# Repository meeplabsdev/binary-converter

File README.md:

# Binary Converter

Need to quickly convert a decimal or hex number (0-F) into binary? Now you can, with the press of two buttons.

## Schematic

## PCB

## How to build
Just order the PCB & components, open up the KiCAD file and build it accordingly.

## BOM
- 2 	Battery holder
- 8	  NPN Transistor
- 8 	47k Resistor
- 4  	4.7k Resistor
- 4 	220 Resistor
- 1 	Potentiometer
- 8 	Push Button
- 4   LED

Made by [`@19benfielde (<@U08JNMG6L00>)`](https://hackclub.slack.com/team/U08JNMG6L00) on slack :D

Made as a part of http://solder.hackclub.com/!

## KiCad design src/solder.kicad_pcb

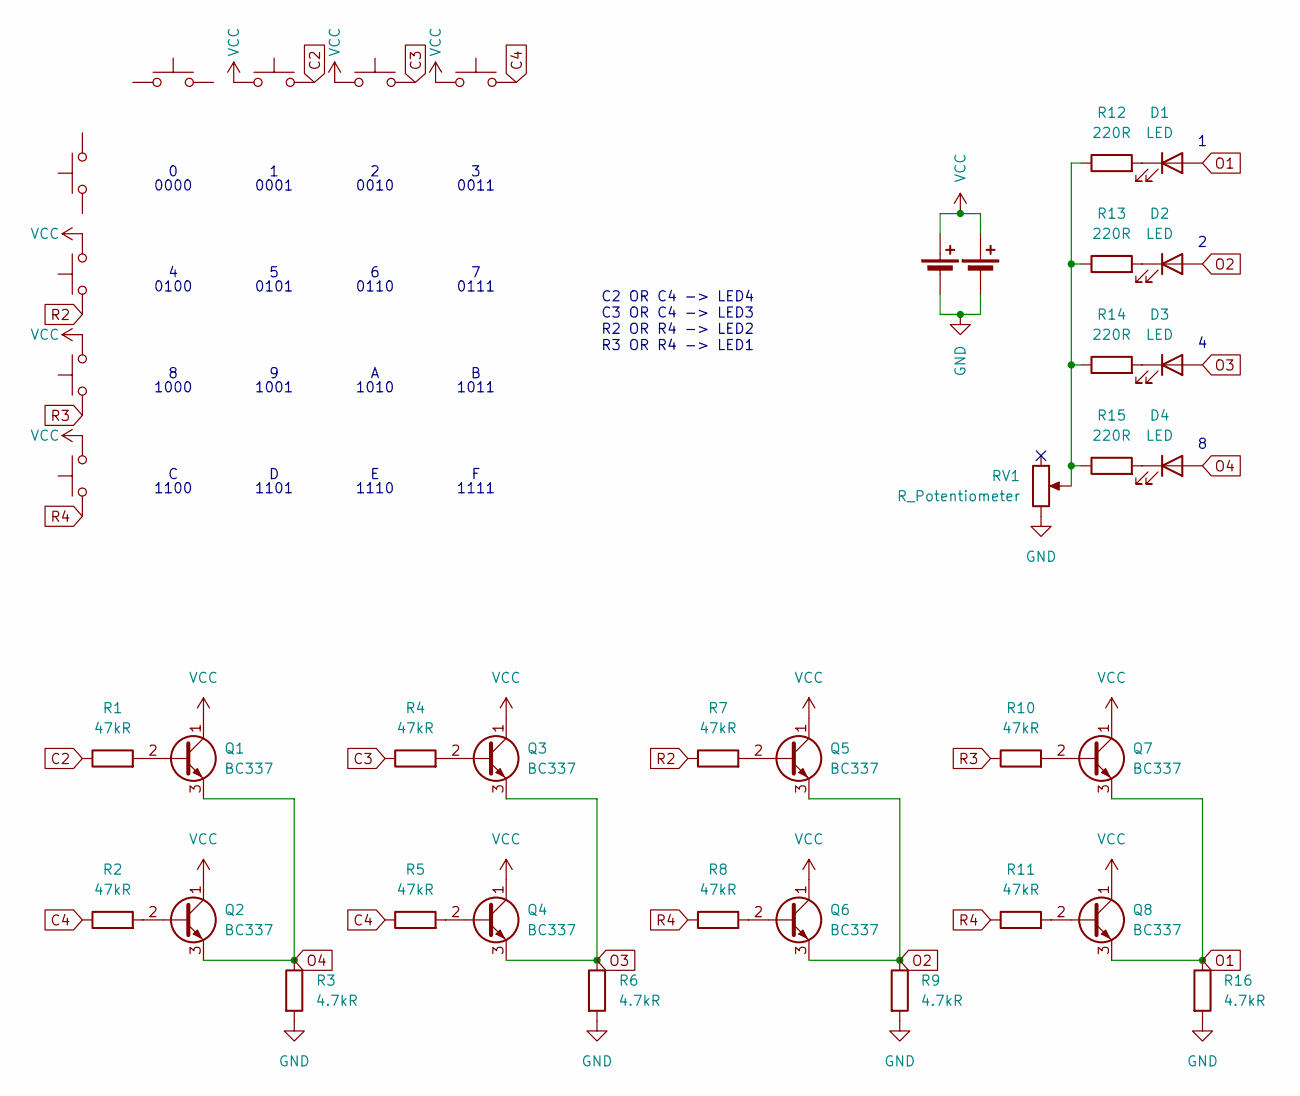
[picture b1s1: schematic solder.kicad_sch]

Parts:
BT1, BT2: Battery_Cell; BatteryHolder_Keystone_3034_1x20mm
D1, D2, D3, D4: LED; LED_D5.0mm
Q1, Q2, Q3, Q4, Q5, Q6, Q7, Q8: BC337; TO-92_Inline
R1, R2, R4, R5, R7, R8, R10, R11: 47kR; R_Axial_DIN0207_L6.3mm_D2.5mm_P7.62mm_Horizontal
R3, R6, R9, R16: 4.7kR; R_Axial_DIN0207_L6.3mm_D2.5mm_P7.62mm_Horizontal
R12, R13, R14, R15: 220R; R_Axial_DIN0207_L6.3mm_D2.5mm_P7.62mm_Horizontal
RV1: R_Potentiometer; Potentiometer_Vishay_T73YP_Vertical
SW1, SW2, SW3, SW4, SW5, SW6, SW7, SW8: SW_Push; SW_PUSH_6mm

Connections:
C2: R1.1, SW6.2
C3: R4.1, SW7.2
C4: R2.1, R5.1, SW8.2
GND: BT1.2 (-), BT2.2 (-), R3.2, R6.2, R9.2, R16.2, RV1.3
unnamed: D1.1 (K), R12.2
unnamed: D2.1 (K), R13.2
unnamed: D3.1 (K), R14.2
unnamed: D4.1 (K), R15.2
unnamed: Q1.2 (B), R1.2
unnamed: Q2.2 (B), R2.2
unnamed: Q3.2 (B), R4.2
unnamed: Q4.2 (B), R5.2
unnamed: Q5.2 (B), R7.2
unnamed: Q6.2 (B), R8.2
unnamed: Q7.2 (B), R10.2
unnamed: Q8.2 (B), R11.2
unnamed: R12.1, R13.1, R14.1, R15.1, RV1.2
O1: D1.2 (A), Q7.3 (E), Q8.3 (E), R16.1
O2: D2.2 (A), Q5.3 (E), Q6.3 (E), R9.1
O3: D3.2 (A), Q3.3 (E), Q4.3 (E), R6.1
O4: D4.2 (A), Q1.3 (E), Q2.3 (E), R3.1
R2: R7.1, SW2.1
R3: R10.1, SW3.1
R4: R8.1, R11.1, SW4.1
VCC: BT1.1 (+), BT2.1 (+), Q1.1 (C), Q2.1 (C), Q3.1 (C), Q4.1 (C), Q5.1 (C), Q6.1 (C), Q7.1 (C), Q8.1 (C), SW2.2, SW3.2, SW4.2, SW6.1, SW7.1, SW8.1

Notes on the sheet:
1110
0000
0111
1000
0101
0110
0100
1101
1001
0001
1100
1010
0011
1111
C2 OR C4 -> LED4 C3 OR C4 -> LED3 R2 OR R4 -> LED2 R3 OR R4 -> LED1
1011
0010

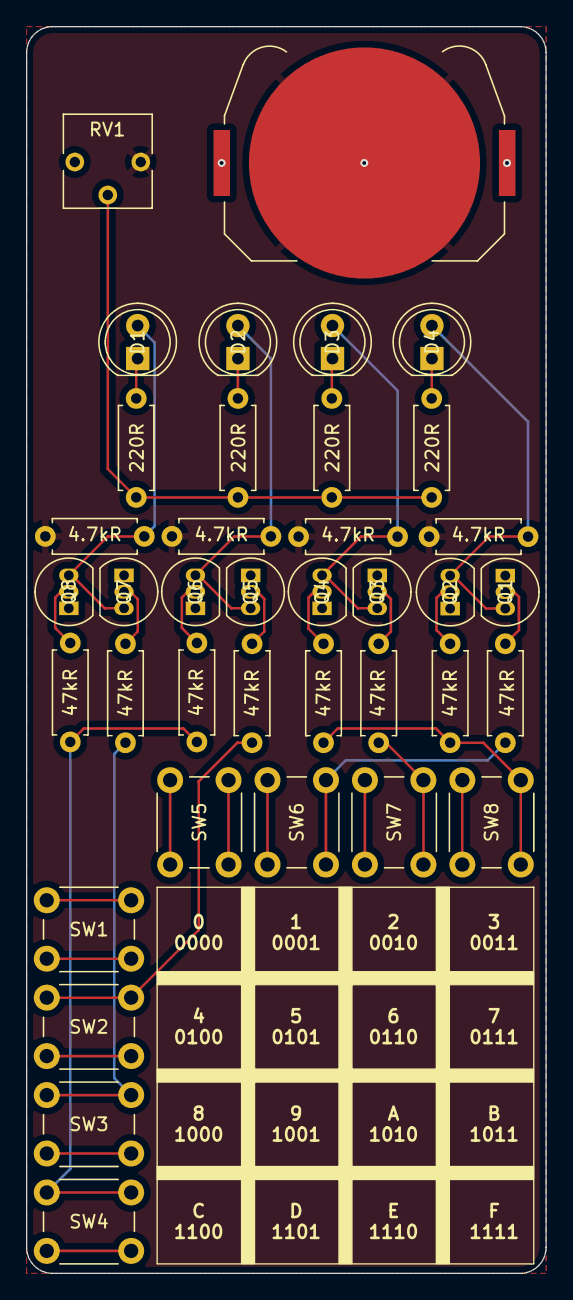
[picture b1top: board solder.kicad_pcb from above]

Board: 2 copper layers, 40.0 x 96.0 mm, 39 parts (1 on the bottom side), 25 nets.

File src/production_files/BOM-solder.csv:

Comment,Designator,Footprint,LCSC,Quantity
LED,D4,LED_D5.0mm,,1
LED,D1,LED_D5.0mm,,1
LED,D2,LED_D5.0mm,,1
LED,D3,LED_D5.0mm,,1
220R,R15,R_Axial_DIN0207_L6.3mm_D2.5mm_P7.62mm_Horizontal,,1
220R,R13,R_Axial_DIN0207_L6.3mm_D2.5mm_P7.62mm_Horizontal,,1
220R,R12,R_Axial_DIN0207_L6.3mm_D2.5mm_P7.62mm_Horizontal,,1
220R,R14,R_Axial_DIN0207_L6.3mm_D2.5mm_P7.62mm_Horizontal,,1
47kR,R2,R_Axial_DIN0207_L6.3mm_D2.5mm_P7.62mm_Horizontal,,1
47kR,R1,R_Axial_DIN0207_L6.3mm_D2.5mm_P7.62mm_Horizontal,,1
4.7kR,R3,R_Axial_DIN0207_L6.3mm_D2.5mm_P7.62mm_Horizontal,,1
BC337,Q2,TO-92_Inline,,1
BC337,Q1,TO-92_Inline,,1
47kR,R4,R_Axial_DIN0207_L6.3mm_D2.5mm_P7.62mm_Horizontal,,1
47kR,R5,R_Axial_DIN0207_L6.3mm_D2.5mm_P7.62mm_Horizontal,,1
4.7kR,R16,R_Axial_DIN0207_L6.3mm_D2.5mm_P7.62mm_Horizontal,,1
BC337,Q3,TO-92_Inline,,1
BC337,Q4,TO-92_Inline,,1
47kR,R10,R_Axial_DIN0207_L6.3mm_D2.5mm_P7.62mm_Horizontal,,1
4.7kR,R9,R_Axial_DIN0207_L6.3mm_D2.5mm_P7.62mm_Horizontal,,1
47kR,R11,R_Axial_DIN0207_L6.3mm_D2.5mm_P7.62mm_Horizontal,,1
BC337,Q8,TO-92_Inline,,1
BC337,Q7,TO-92_Inline,,1
BC337,Q5,TO-92_Inline,,1
BC337,Q6,TO-92_Inline,,1
4.7kR,R6,R_Axial_DIN0207_L6.3mm_D2.5mm_P7.62mm_Horizontal,,1
47kR,R7,R_Axial_DIN0207_L6.3mm_D2.5mm_P7.62mm_Horizontal,,1
47kR,R8,R_Axial_DIN0207_L6.3mm_D2.5mm_P7.62mm_Horizontal,,1
SW_Push,SW8,SW_PUSH_6mm,,1
SW_Push,SW6,SW_PUSH_6mm,,1
SW_Push,SW5,SW_PUSH_6mm,,1
SW_Push,SW4,SW_PUSH_6mm,,1
SW_Push,SW3,SW_PUSH_6mm,,1
SW_Push,SW2,SW_PUSH_6mm,,1
SW_Push,SW1,SW_PUSH_6mm,,1
R_Potentiometer,RV1,Potentiometer_Vishay_T73YP_Vertical,,1
Battery_Cell,BT2,BatteryHolder_Keystone_3034_1x20mm,,1
Battery_Cell,BT1,BatteryHolder_Keystone_3034_1x20mm,,1
SW_Push,SW7,SW_PUSH_6mm,,1

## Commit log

2025-05-21 Create LICENSE
